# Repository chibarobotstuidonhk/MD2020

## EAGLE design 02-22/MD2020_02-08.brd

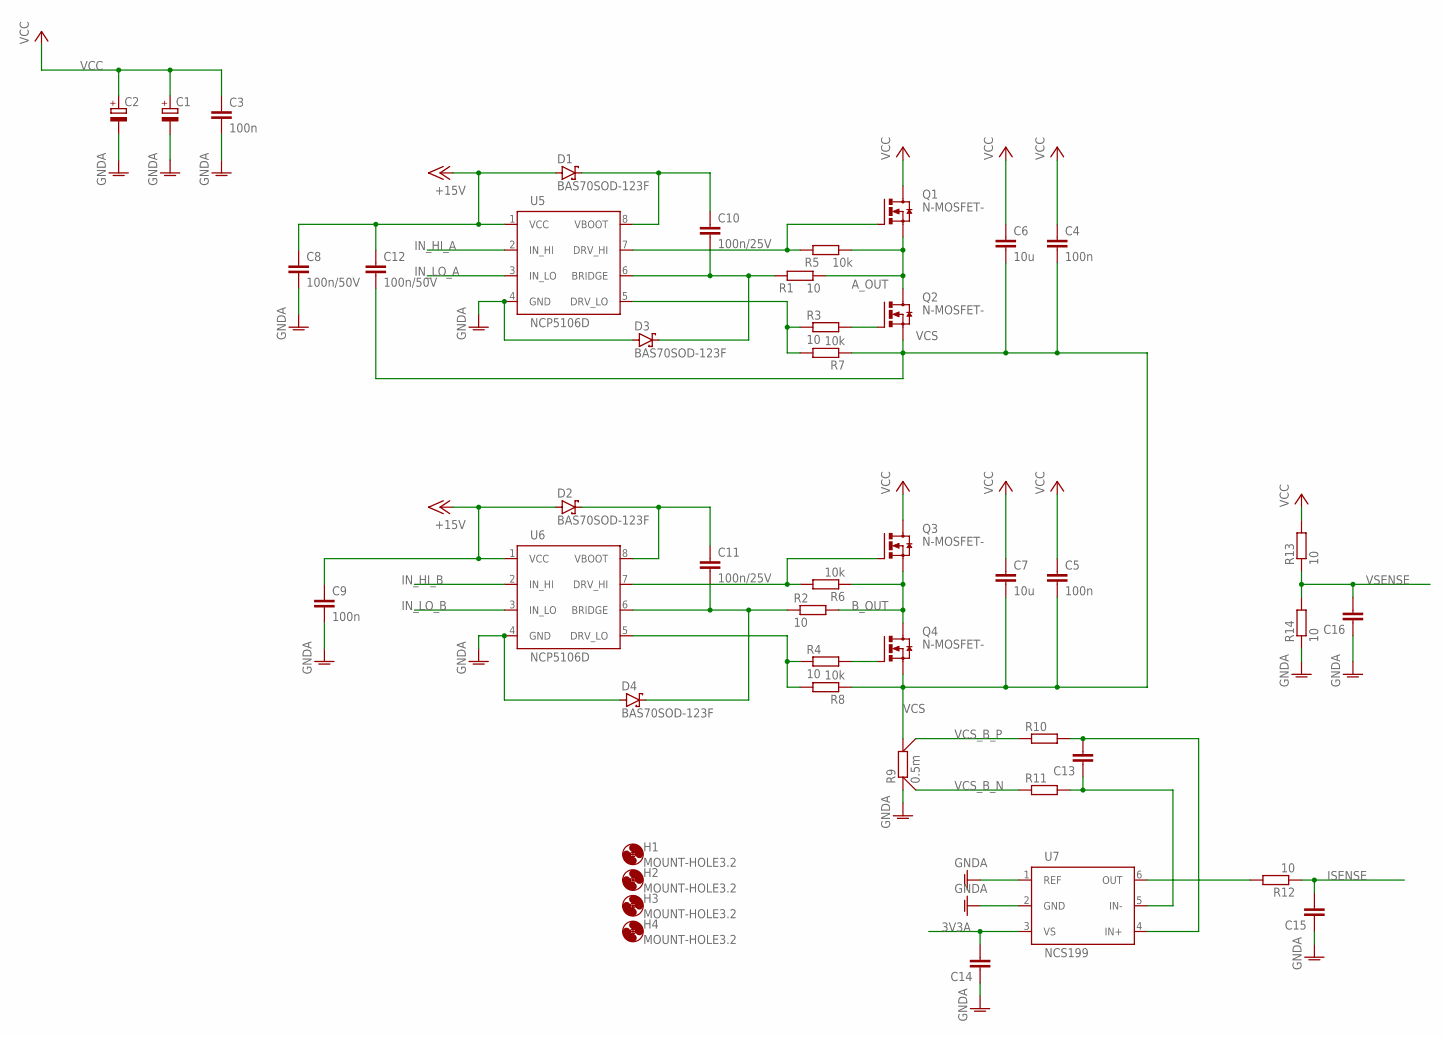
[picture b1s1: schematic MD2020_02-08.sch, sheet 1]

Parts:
C1, C2: CPOL-EUE5-10.5; E5-10,5
C3, C4, C5, C9: 100n; C0603; MPN CC0603KRX7R9BB104
C6, C7: 10u; C1210; MPN CL31A106KBHNNNE
C8, C12: 100n/50V; C0603; MPN CC0603KRX7R9BB104
C10, C11: 100n/25V; C0603; MPN CC0603KRX7R9BB104
C13, C14, C15, C16: C-EUC0603; C0603
D1, D2, D3, D4: BAS70SOD-123F; SOD123F; MPN PMEG4010EH,115
H1, H2, H3, H4: MOUNT-HOLE3.2; 3,2
Q1, Q2, Q3, Q4: N-MOSFET-; SOT669
R1, R2, R3, R4, R12, R13, R14: 10; R0603; MPN RC0603FR-0710RL
R5, R6, R7, R8: 10k; R0603; MPN RC0603FR-0710KL
R9: 0.5m; CSS2H-2512
R10, R11: R-EU_R0603; R0603
U5, U6: NCP5106D; SOIC127P600X175-8
U7: NCS199; SOT65P210X110-6

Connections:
3V3A: C14.2, U7.3 (VS); also elsewhere on the board
+15V: C8.1, C9.1, C12.1, D1.A, D2.A, U5.1 (VCC), U6.1 (VCC); also elsewhere on the board
A_OUT: Q1.1 (SOURCE), Q1.2 (SOURCE), Q1.3 (SOURCE), Q2.5 (DRAIN), R1.2, R5.1
B_OUT: Q3.1 (SOURCE), Q3.2 (SOURCE), Q3.3 (SOURCE), Q4.5 (DRAIN), R2.2, R6.1
GNDA: C1.-, C2.-, C3.2, C8.2, C9.2, C14.1, C15.1, C16.1, D3.A, D4.A, R9.1$1 (1), R9.1$2 (1), R14.1, U5.4 (GND), U6.4 (GND), U7.1 (REF), U7.2 (GND); also elsewhere on the board
IN_HI_A: U5.2 (IN_HI); also elsewhere on the board
IN_HI_B: U6.2 (IN_HI); also elsewhere on the board
IN_LO_A: U5.3 (IN_LO); also elsewhere on the board
IN_LO_B: U6.3 (IN_LO); also elsewhere on the board
ISENSE: C15.2, R12.1; also elsewhere on the board
unnamed: Q1.4 (GATE), R5.2, U5.7 (DRV_HI)
unnamed: Q3.4 (GATE), R6.2, U6.7 (DRV_HI)
unnamed: C10.2, D3.C, R1.1, U5.6 (BRIDGE)
unnamed: R4.1, R8.2, U6.5 (DRV_LO)
unnamed: R12.2, U7.6 (OUT)
unnamed: R3.1, R7.2, U5.5 (DRV_LO)
unnamed: C11.2, D4.C, R2.1, U6.6 (BRIDGE)
unnamed: C13.2, R10.2, U7.4 (IN+)
unnamed: C13.1, R11.2, U7.5 (IN-)
unnamed: Q2.4 (GATE), R3.2
unnamed: Q4.4 (GATE), R4.2
unnamed: C11.1, D2.C, U6.8 (VBOOT)
unnamed: C10.1, D1.C, U5.8 (VBOOT)
VCC: C1.+, C2.+, C3.1, C4.1, C5.1, C6.1, C7.1, Q1.5 (DRAIN), Q3.5 (DRAIN), R13.2; also elsewhere on the board
VCS: C4.2, C5.2, C6.2, C7.2, C12.2, Q2.1 (SOURCE), Q2.2 (SOURCE), Q2.3 (SOURCE), Q4.1 (SOURCE), Q4.2 (SOURCE), Q4.3 (SOURCE), R7.1, R8.1, R9.2$1 (2), R9.2$2 (2)
VCS_B_N: R9.1S, R11.1
VCS_B_P: R9.2S, R10.1
VSENSE: C16.2, R13.1, R14.2; also elsewhere on the board

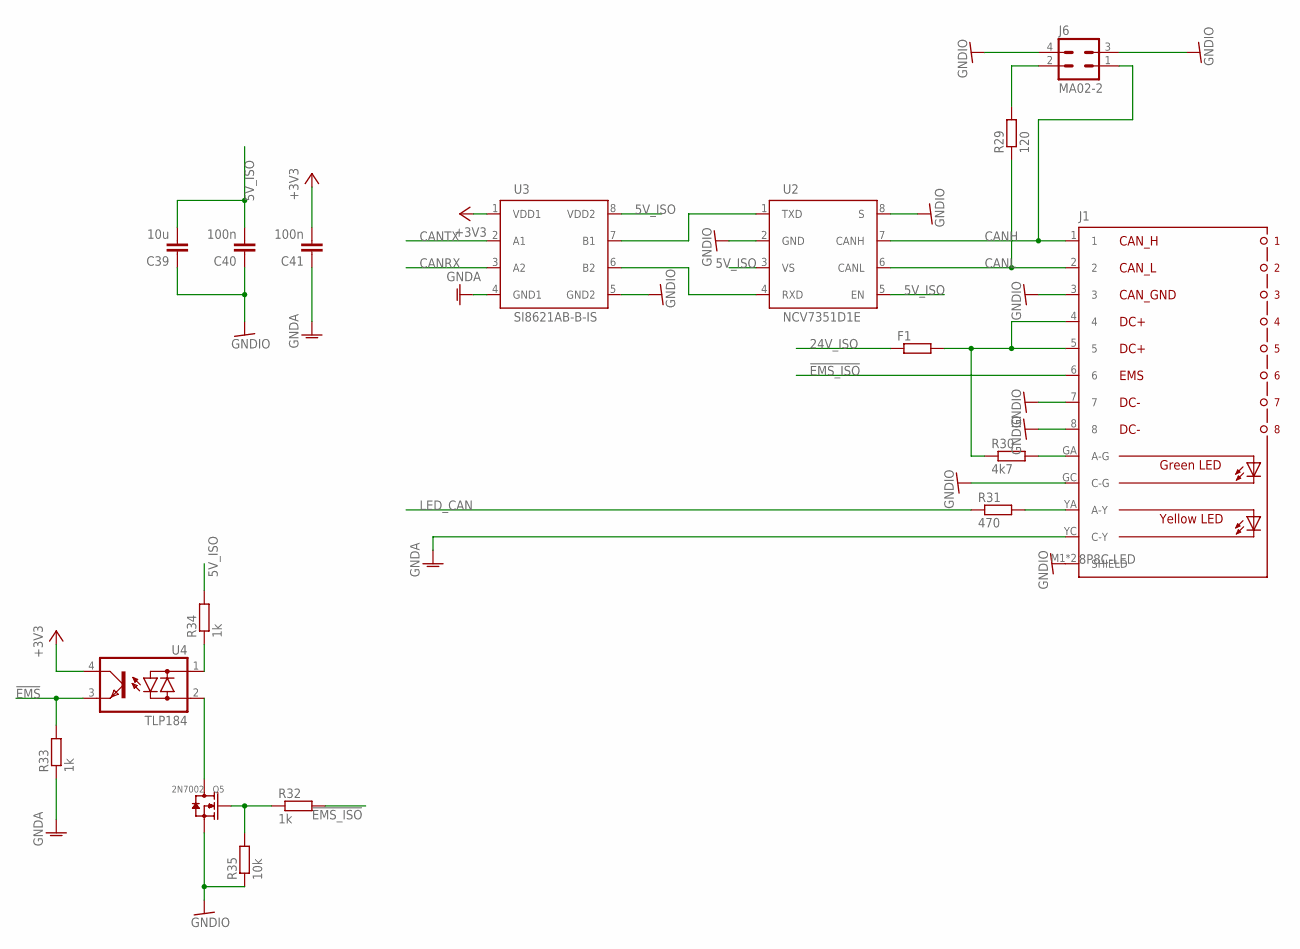
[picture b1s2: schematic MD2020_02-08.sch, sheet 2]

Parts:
C39: 10u; C0805; MPN CC0805ZKY5V6BB106
C40, C41: 100n; C0603; MPN CC0603KRX7R9BB104
F1: R-EU_R1206; R1206
J1: 8P8C-LED
J6: MA02-2; MA02-2W
Q5: 2N7002; SOT-23
R29: 120; R0603; MPN RC0603JR-07120RL
R30: 4k7; R0603; MPN RC0603FR-074K7L
R31: 470; R0603; MPN RC0603JR-07470RL
R32, R33, R34: 1k; R0603; MPN RC0603FR-071KL
R35: 10k; R0603; MPN RC0603FR-0710KL
U2: NCV7351D1E; SO08
U3: SI8621AB-B-IS; SO08
U4: TLP184; 11-4M1S

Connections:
5V_ISO: C39.2, C40.2, R34.2, U2.3 (VS), U2.5 (EN), U3.8 (VDD2); also elsewhere on the board
24V_ISO: F1.1; also elsewhere on the board
!EMS: R33.2, U4.3 (E); also elsewhere on the board
!EMS_ISO: J1.6, R32.2
+3V3: C41.2, U3.1 (VDD1), U4.4 (C); also elsewhere on the board
CANH: J1.1, J6.1, U2.7 (CANH)
CANL: J1.2, R29.1, U2.6 (CANL)
CANRX: U3.3 (A2); also elsewhere on the board
CANTX: U3.2 (A1); also elsewhere on the board
GNDA: C41.1, J1.YC (C-Y), R33.1, U3.4 (GND1); also elsewhere on the board
GNDIO: C39.1, C40.1, J1.3, J1.7, J1.8, J1.GC (C-G), J1.M1 (SHIELD), J1.M2 (SHIELD), J6.3, J6.4, Q5.2 (S), R35.1, U2.2 (GND), U2.8 (S), U3.5 (GND2); also elsewhere on the board
LED_CAN: R31.1; also elsewhere on the board
unnamed: F1.2, J1.4, J1.5, R30.1
unnamed: J6.2, R29.2
unnamed: J1.GA (A-G), R30.2
unnamed: J1.YA (A-Y), R31.2
unnamed: Q5.1 (G), R32.1, R35.2
unnamed: U2.1 (TXD), U3.7 (B1)
unnamed: U2.4 (RXD), U3.6 (B2)
unnamed: Q5.3 (D), U4.2 (AC2)
unnamed: R34.1, U4.1 (AC1)

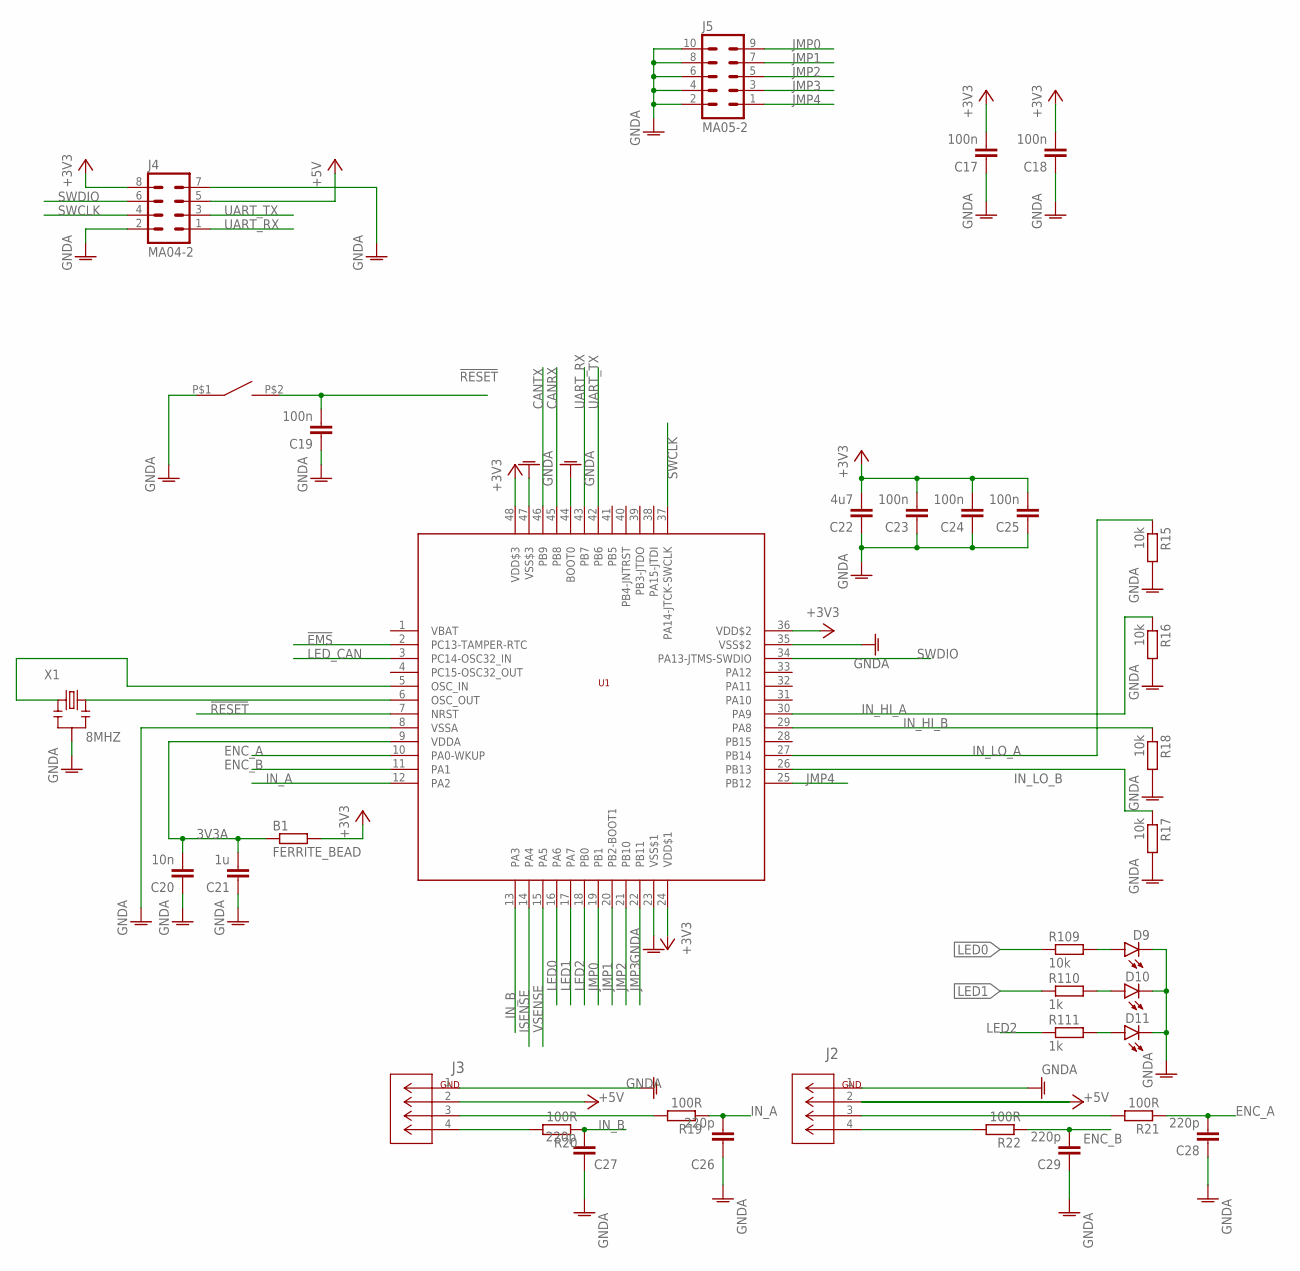
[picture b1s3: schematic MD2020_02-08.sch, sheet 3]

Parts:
B1: FERRITE_BEAD; R0603
C17, C18, C19, C23, C24, C25: 100n; C0603; MPN CC0603KRX7R9BB104
C20: 10n; C0603
C21: 1u; C0603; MPN CC0603KRX7R8BB105
C22: 4u7; C0805; MPN CC0603KRX5R6BB475
C26, C27, C28, C29: 220p; C0603; MPN CL10B221KB8NNNC
D9, D10, D11: LEDCHIPLED_0805; CHIPLED_0805
J2, J3: 1744426-4; CONN4_1744426-4
J4: MA04-2; MA04-2W
J5: MA05-2; MA05-2W
R15, R16, R17, R18, R109: 10k; R0603; MPN RC0603FR-0710KL
R19, R20, R21, R22: 100R; R0603; MPN RC0603JR-07100RL
R110, R111: 1k; R0603; MPN RC0603FR-071KL
S1: SWITCH_TACTILETOP; SWITCH_TACTILE_3X6
U1: STM32F103C8; LQFP48; MPN STM32F103C8T6
X1: 8MHZ; X3-SMD-3.6X1.3X0.8MM; MPN CSTCE8M00G55-RO

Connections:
3V3A: B1.1, C20.2, C21.2, U1.9 (VDDA); also elsewhere on the board
!EMS: U1.2 (PC13-TAMPER-RTC); also elsewhere on the board
!RESET: C19.2, S1.P$2 (2), U1.7 (NRST)
+3V3: B1.2, C17.2, C18.2, C22.2, C23.2, C24.2, C25.2, J4.8, U1.24 (VDD$1), U1.36 (VDD$2), U1.48 (VDD$3); also elsewhere on the board
+5V: J2.2, J3.2, J4.5; also elsewhere on the board
CANRX: U1.45 (PB8); also elsewhere on the board
CANTX: U1.46 (PB9); also elsewhere on the board
ENC_A: C28.2, R21.1, U1.10 (PA0-WKUP)
ENC_B: C29.2, R22.1, U1.11 (PA1)
GNDA: C17.1, C18.1, C19.1, C20.1, C21.1, C22.1, C23.1, C24.1, C25.1, C26.1, C27.1, C28.1, C29.1, D9.C, D10.C, D11.C, J2.1, J3.1, J4.2, J4.7, J5.2, J5.4, J5.6, J5.8, J5.10, R15.2, R16.2, R17.2, R18.2, S1.P$1 (1), U1.8 (VSSA), U1.23 (VSS$1), U1.35 (VSS$2), U1.44 (BOOT0), U1.47 (VSS$3), X1.2; also elsewhere on the board
IN_A: C26.2, R19.1, U1.12 (PA2)
IN_B: C27.2, R20.1, U1.13 (PA3)
IN_HI_A: R16.1, U1.30 (PA9); also elsewhere on the board
IN_HI_B: R18.1, U1.29 (PA8); also elsewhere on the board
IN_LO_A: R15.1, U1.27 (PB14); also elsewhere on the board
IN_LO_B: R17.1, U1.26 (PB13); also elsewhere on the board
ISENSE: U1.14 (PA4); also elsewhere on the board
JMP0: J5.9, U1.19 (PB1)
JMP1: J5.7, U1.20 (PB2-BOOT1)
JMP2: J5.5, U1.21 (PB10)
JMP3: J5.3, U1.22 (PB11)
JMP4: J5.1, U1.25 (PB12)
LED0: R109.1, U1.16 (PA6)
LED1: R110.1, U1.17 (PA7)
LED2: R111.1, U1.18 (PB0)
LED_CAN: U1.3 (PC14-OSC32_IN); also elsewhere on the board
unnamed: D10.A, R110.2
unnamed: D9.A, R109.2
unnamed: U1.6 (OSC_OUT), X1.3
unnamed: J2.4, R22.2
unnamed: J3.4, R20.2
unnamed: J2.3, R21.2
unnamed: J3.3, R19.2
unnamed: U1.5 (OSC_IN), X1.1
unnamed: D11.A, R111.2
SWCLK: J4.4, U1.37 (PA14-JTCK-SWCLK)
SWDIO: J4.6, U1.34 (PA13-JTMS-SWDIO)
UART_RX: J4.1, U1.43 (PB7)
UART_TX: J4.3, U1.42 (PB6)
VSENSE: U1.15 (PA5); also elsewhere on the board

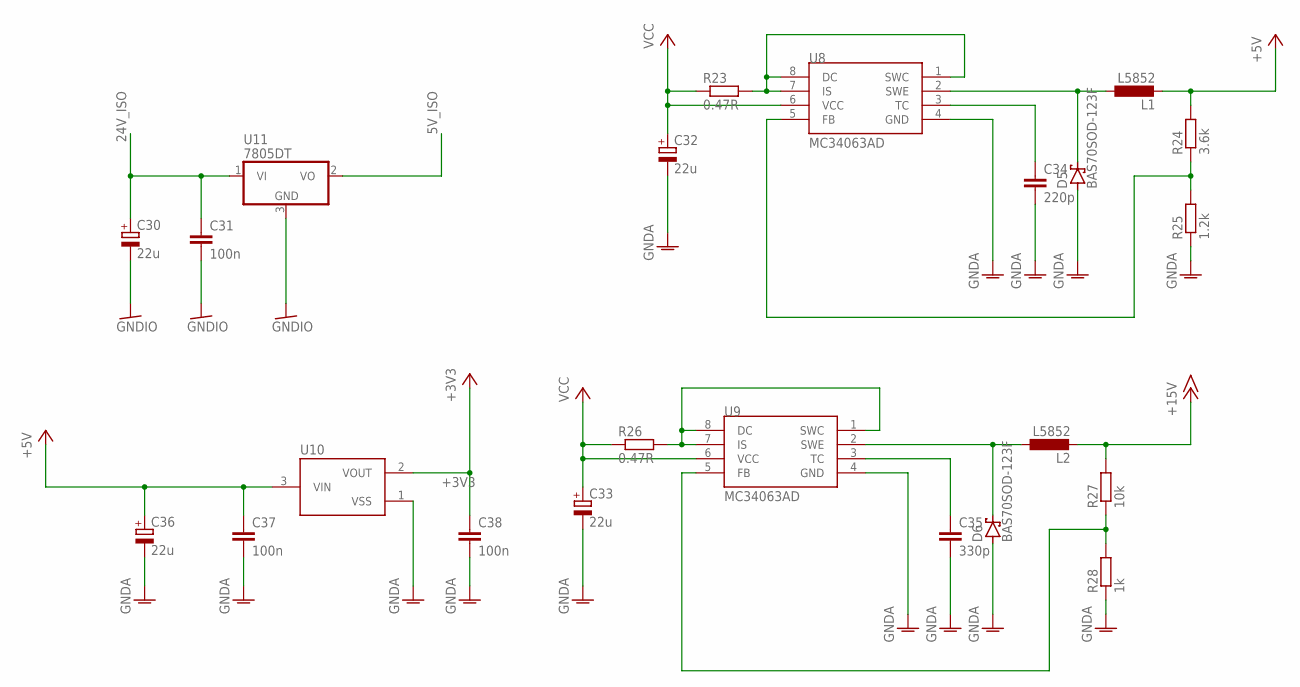
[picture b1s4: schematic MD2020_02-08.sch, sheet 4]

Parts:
C30, C36: 22u; E2,5-5
C31, C37, C38: 100n; C0603; MPN CC0603KRX7R9BB104
C32, C33: 22u; E2-5
C34: 220p; C0603; MPN CL10B221KB8NNNC
C35: 330p; C0603; MPN CL10B331KB8NNNC
D5, D6: BAS70SOD-123F; SOD123F; MPN PMEG4010EH,115
L1, L2: L5852
R23, R26: 0.47R; R0603; MPN 0603WAF470LT5E
R24: 3.6k; R0603; MPN RC0603JR-073K6L
R25: 1.2k; R0603; MPN RC0603JR-071K2L
R27: 10k; R0603; MPN RC0603FR-0710KL
R28: 1k; R0603; MPN RC0603FR-071KL
U8, U9: MC34063AD; SOIC8; MPN MC34063ADR2G
U10: XC6206; SOT95P240X110-3
U11: 7805DT; TO252

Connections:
5V_ISO: U11.2 (VO); also elsewhere on the board
24V_ISO: C30.+, C31.1, U11.1 (VI); also elsewhere on the board
+3V3: C38.1, U10.2 (VOUT); also elsewhere on the board
+5V: C36.+, C37.1, L1.P$2 (2), R24.2, U10.3 (VIN); also elsewhere on the board
+15V: L2.P$2 (2), R27.2; also elsewhere on the board
GNDA: C32.-, C33.-, C34.2, C35.2, C36.-, C37.2, C38.2, D5.A, D6.A, R25.1, R28.1, U8.4 (GND), U9.4 (GND), U10.1 (VSS); also elsewhere on the board
GNDIO: C30.-, C31.2, U11.3 (GND); also elsewhere on the board
unnamed: R23.2, U8.1 (SWC), U8.7 (IS), U8.8 (DC)
unnamed: D5.C, L1.P$1 (1), U8.2 (SWE)
unnamed: C34.1, U8.3 (TC)
unnamed: R24.1, R25.2, U8.5 (FB)
unnamed: R26.2, U9.1 (SWC), U9.7 (IS), U9.8 (DC)
unnamed: D6.C, L2.P$1 (1), U9.2 (SWE)
unnamed: C35.1, U9.3 (TC)
unnamed: R27.1, R28.2, U9.5 (FB)
VCC: C32.+, C33.+, R23.1, R26.1, U8.6 (VCC), U9.6 (VCC); also elsewhere on the board

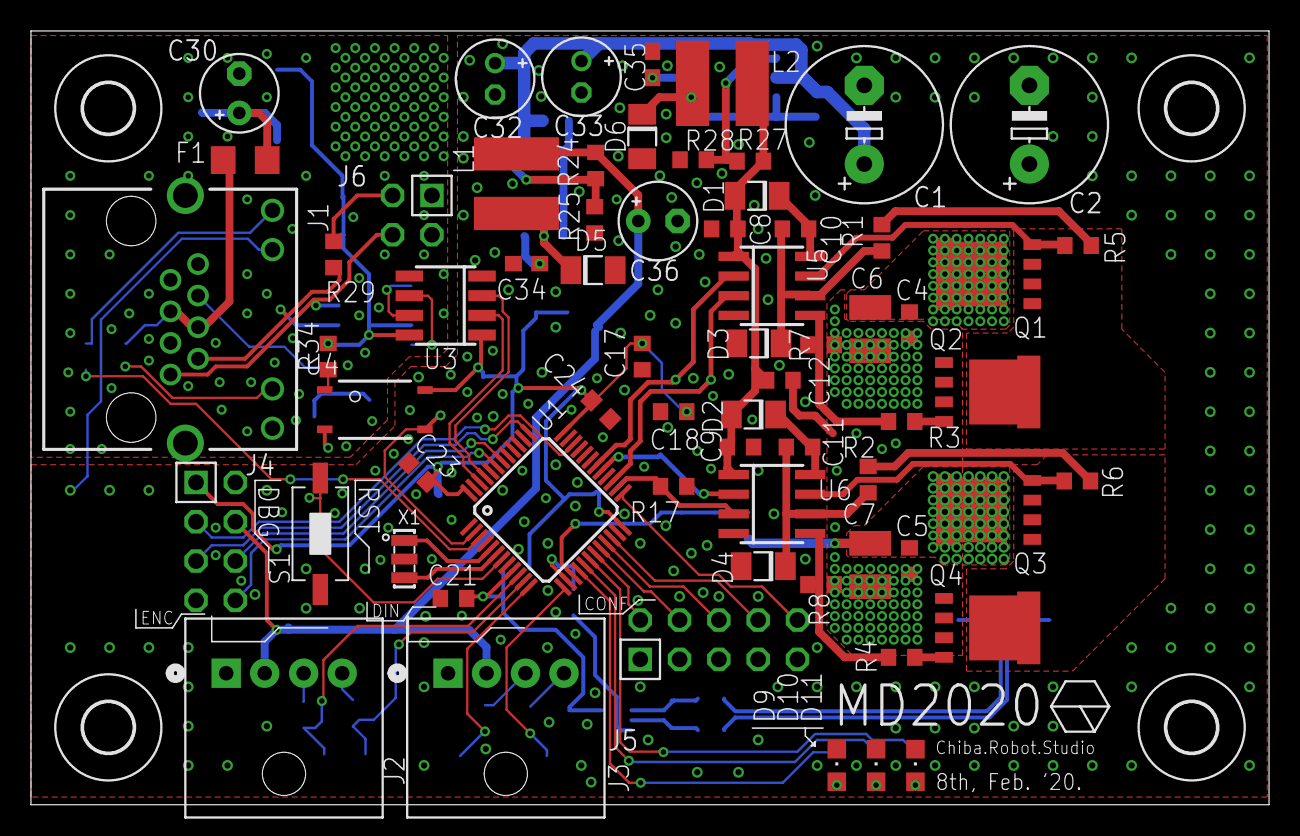
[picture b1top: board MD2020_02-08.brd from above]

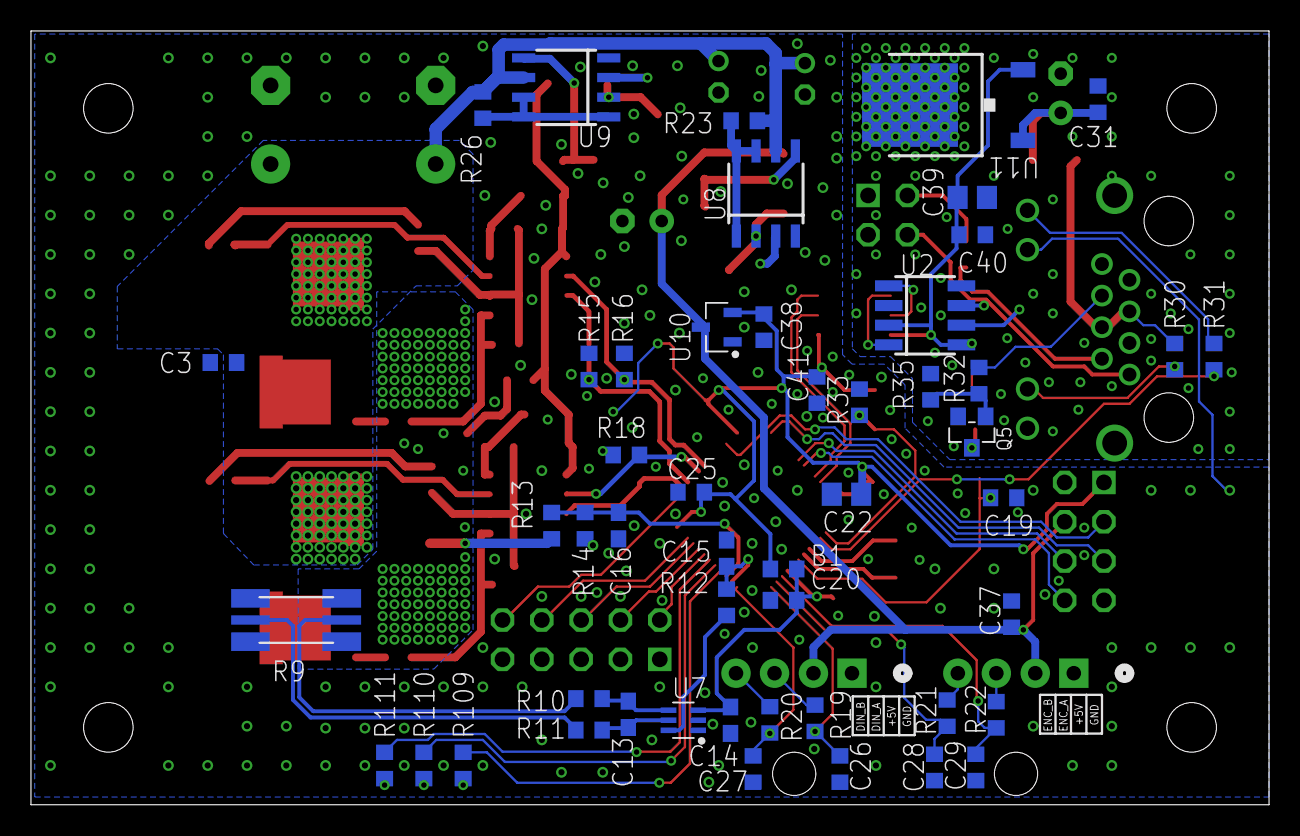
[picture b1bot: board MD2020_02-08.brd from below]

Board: 2 copper layers, 80.0 x 50.0 mm, 120 parts (50 on the bottom side), 83 nets.

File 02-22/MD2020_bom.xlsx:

Part | Value | Device | Package | Description | MPN | 製品詳細セイヒンショウサイ
C3 | 100n | C-EUC0603 | C0603 | CAPACITOR | CC0603KRX7R9BB104 | SMD CAP Ceramic 100nF-50V-10%-X7R
C4 | 100n | C-EUC0603 | C0603 | CAPACITOR | CC0603KRX7R9BB104 | SMD CAP Ceramic 100nF-50V-10%-X7R
C5 | 100n | C-EUC0603 | C0603 | CAPACITOR | CC0603KRX7R9BB104 | SMD CAP Ceramic 100nF-50V-10%-X7R
C6 | 10u | C-EUC1210 | C1210 | CAPACITOR | CL31A106KBHNNNE | 1206 10uF ±10% 50V X5R
C7 | 10u | C-EUC1210 | C1210 | CAPACITOR | CL31A106KBHNNNE | 1206 10uF ±10% 50V X5R
C8 | 100n/50V | C-EUC0603 | C0603 | CAPACITOR | CC0603KRX7R9BB104 | SMD CAP Ceramic 100nF-50V-10%-X7R
C9 | 100n | C-EUC0603 | C0603 | CAPACITOR | CC0603KRX7R9BB104 | SMD CAP Ceramic 100nF-50V-10%-X7R
C10 | 100n/25V | C-EUC0603 | C0603 | CAPACITOR | CC0603KRX7R9BB104 | SMD CAP Ceramic 100nF-50V-10%-X7R
C11 | 100n/25V | C-EUC0603 | C0603 | CAPACITOR | CC0603KRX7R9BB104 | SMD CAP Ceramic 100nF-50V-10%-X7R
C12 | 100n/50V | C-EUC0603 | C0603 | CAPACITOR | CC0603KRX7R9BB104 | SMD CAP Ceramic 100nF-50V-10%-X7R
C17 | 100n | C-EUC0603 | C0603 | CAPACITOR | CC0603KRX7R9BB104 | SMD CAP Ceramic 100nF-50V-10%-X7R
C18 | 100n | C-EUC0603 | C0603 | CAPACITOR | CC0603KRX7R9BB104 | SMD CAP Ceramic 100nF-50V-10%-X7R
C19 | 100n | C-EUC0603 | C0603 | CAPACITOR | CC0603KRX7R9BB104 | SMD CAP Ceramic 100nF-50V-10%-X7R
C21 | 1u | C-EUC0603 | C0603 | CAPACITOR | CC0603KRX7R8BB105 | SMD CAP Ceramic 1uF-25V-10%-X7R
C22 | 4u7 | C-EUC0805 | C0805 | CAPACITOR | CC0603KRX5R6BB475 | SMD CAP Ceramic 4.7uF-10V-10%-X5R;
C23 | 100n | C-EUC0603 | C0603 | CAPACITOR | CC0603KRX7R9BB104 | SMD CAP Ceramic 100nF-50V-10%-X7R
C24 | 100n | C-EUC0603 | C0603 | CAPACITOR | CC0603KRX7R9BB104 | SMD CAP Ceramic 100nF-50V-10%-X7R
C25 | 100n | C-EUC0603 | C0603 | CAPACITOR | CC0603KRX7R9BB104 | SMD CAP Ceramic 100nF-50V-10%-X7R
C26 | 220p | C-EUC0603 | C0603 | CAPACITOR | CL10B221KB8NNNC | 0603 220pF ±10% 50V X7R
C27 | 220p | C-EUC0603 | C0603 | CAPACITOR | CL10B221KB8NNNC | 0603 220pF ±10% 50V X7R
C28 | 220p | C-EUC0603 | C0603 | CAPACITOR | CL10B221KB8NNNC | 0603 220pF ±10% 50V X7R
C29 | 220p | C-EUC0603 | C0603 | CAPACITOR | CL10B221KB8NNNC | 0603 220pF ±10% 50V X7R
C31 | 100n | C-EUC0603 | C0603 | CAPACITOR | CC0603KRX7R9BB104 | SMD CAP Ceramic 100nF-50V-10%-X7R
C34 | 220p | C-EUC0603 | C0603 | CAPACITOR | CL10B221KB8NNNC | 0603 220pF ±10% 50V X7R
C35 | 330p | C-EUC0603 | C0603 | CAPACITOR | CL10B331KB8NNNC | 0603 330pF ±10% 50V X7R
C37 | 100n | C-EUC0603 | C0603 | CAPACITOR | CC0603KRX7R9BB104 | SMD CAP Ceramic 100nF-50V-10%-X7R
C38 | 100n | C-EUC0603 | C0603 | CAPACITOR | CC0603KRX7R9BB104 | SMD CAP Ceramic 100nF-50V-10%-X7R
C39 | 10u | C-EUC0805 | C0805 | CAPACITOR | CC0805ZKY5V6BB106 | SMD CAP Ceramic 10uF-10V-(-20%
C40 | 100n | C-EUC0603 | C0603 | CAPACITOR | CC0603KRX7R9BB104 | SMD CAP Ceramic 100nF-50V-10%-X7R
C41 | 100n | C-EUC0603 | C0603 | CAPACITOR | CC0603KRX7R9BB104 | SMD CAP Ceramic 100nF-50V-10%-X7R
D1 | BAS70SOD-123F | BAS70SOD-123F | SOD123F | Silicon Schottky Diodes | PMEG4010EH,115 | DIODE SCHOTTKY 40V 1A SOD123F
D2 | BAS70SOD-123F | BAS70SOD-123F | SOD123F | Silicon Schottky Diodes | PMEG4010EH,115 | DIODE SCHOTTKY 40V 1A SOD123F
D3 | BAS70SOD-123F | BAS70SOD-123F | SOD123F | Silicon Schottky Diodes | PMEG4010EH,115 | DIODE SCHOTTKY 40V 1A SOD123F
D4 | BAS70SOD-123F | BAS70SOD-123F | SOD123F | Silicon Schottky Diodes | PMEG4010EH,115 | DIODE SCHOTTKY 40V 1A SOD123F
D5 | BAS70SOD-123F | BAS70SOD-123F | SOD123F | Silicon Schottky Diodes | PMEG4010EH,115 | DIODE SCHOTTKY 40V 1A SOD123F
D6 | BAS70SOD-123F | BAS70SOD-123F | SOD123F | Silicon Schottky Diodes | PMEG4010EH,115 | DIODE SCHOTTKY 40V 1A SOD123F
Q5 | 2N7002 | SMD-MOSFET-N-CH-60V-300MA-LOGIC-LEVEL-FET-2N7002(SOT-23) | SOT-23 | 305030028 | 2N7002,215 | SMD MOSFET N-CH 60V 300mA
R1 | 10R | R-EU_R0603 | R0603 | RESISTOR | RC0603FR-0710RL | SMD RES 10R-1%-1/10W
R2 | 10R | R-EU_R0603 | R0603 | RESISTOR | RC0603FR-0710RL | SMD RES 10R-1%-1/10W
R3 | 10R | R-EU_R0603 | R0603 | RESISTOR | RC0603FR-0710RL | SMD RES 10R-1%-1/10W
R4 | 10R | R-EU_R0603 | R0603 | RESISTOR | RC0603FR-0710RL | SMD RES 10R-1%-1/10W
R5 | 10k | R-EU_R0603 | R0603 | RESISTOR | RC0603FR-0710KL | SMD RES 10K-1%-1/10W
R6 | 10k | R-EU_R0603 | R0603 | RESISTOR | RC0603FR-0710KL | SMD RES 10K-1%-1/10W
R7 | 10k | R-EU_R0603 | R0603 | RESISTOR | RC0603FR-0710KL | SMD RES 10K-1%-1/10W
R8 | 10k | R-EU_R0603 | R0603 | RESISTOR | RC0603FR-0710KL | SMD RES 10K-1%-1/10W
R12 | 10R | R-EU_R0603 | R0603 | RESISTOR | RC0603FR-0710RL | SMD RES 10R-1%-1/10W
R13 | 10R | R-EU_R0603 | R0603 | RESISTOR | RC0603FR-0710RL | SMD RES 10R-1%-1/10W
R14 | 10R | R-EU_R0603 | R0603 | RESISTOR | RC0603FR-0710RL | SMD RES 10R-1%-1/10W
R15 | 10k | R-EU_R0603 | R0603 | RESISTOR | RC0603FR-0710KL | SMD RES 10K-1%-1/10W
R16 | 10k | R-EU_R0603 | R0603 | RESISTOR | RC0603FR-0710KL | SMD RES 10K-1%-1/10W
R17 | 10k | R-EU_R0603 | R0603 | RESISTOR | RC0603FR-0710KL | SMD RES 10K-1%-1/10W
R18 | 10k | R-EU_R0603 | R0603 | RESISTOR | RC0603FR-0710KL | SMD RES 10K-1%-1/10W
R19 | 100R | R-EU_R0603 | R0603 | RESISTOR | RC0603JR-07100RL | SMD RES 100R-5%-1/10W
R20 | 100R | R-EU_R0603 | R0603 | RESISTOR | RC0603JR-07100RL | SMD RES 100R-5%-1/10W
R21 | 100R | R-EU_R0603 | R0603 | RESISTOR | RC0603JR-07100RL | SMD RES 100R-5%-1/10W
R22 | 100R | R-EU_R0603 | R0603 | RESISTOR | RC0603JR-07100RL | SMD RES 100R-5%-1/10W
R23 | 0.47R | R-EU_R0603 | R0603 | RESISTOR | 0603WAF470LT5E | 0603 0.47Ω ±1% 1/10W ±800ppm/℃
R24 | 3.6k | R-EU_R0603 | R0603 | RESISTOR | RC0603JR-073K6L | 0603 3.6KΩ ±5% 1/10W ±100ppm/°C
R25 | 1.2k | R-EU_R0603 | R0603 | RESISTOR | RC0603JR-071K2L | 0603 1.2KΩ ±5% 1/10W ±100ppm/°C
R26 | 0.47R | R-EU_R0603 | R0603 | RESISTOR | 0603WAF470LT5E | 0603 0.47Ω ±1% 1/10W ±800ppm/℃
R27 | 10k | R-EU_R0603 | R0603 | RESISTOR | RC0603FR-0710KL | SMD RES 10K-1%-1/10W
R28 | 1k | R-EU_R0603 | R0603 | RESISTOR | RC0603FR-071KL | SMD RES 1K-1%-1/10W
R29 | 120R | R-EU_R0603 | R0603 | RESISTOR | RC0603JR-07120RL | SMD RES 120R-5%-1/10W;0603
R30 | 4k7 | R-EU_R0603 | R0603 | RESISTOR | RC0603FR-074K7L | SMD RES 4.7K-1%-1/10W;0603
R31 | 470R | R-EU_R0603 | R0603 | RESISTOR | RC0603JR-07470RL | SMD RES 470R-5%-1/10W;0603
R32 | 1k | R-EU_R0603 | R0603 | RESISTOR | RC0603FR-071KL | SMD RES 1K-1%-1/10W
R33 | 1k | R-EU_R0603 | R0603 | RESISTOR | RC0603FR-071KL | SMD RES 1K-1%-1/10W
R34 | 1k | R-EU_R0603 | R0603 | RESISTOR | RC0603FR-071KL | SMD RES 1K-1%-1/10W
R35 | 10k | R-EU_R0603 | R0603 | RESISTOR | RC0603FR-0710KL | SMD RES 10K-1%-1/10W
R109 | 10k | R-EU_R0603 | R0603 | RESISTOR | RC0603FR-0710KL | SMD RES 10K-1%-1/10W
R110 | 1k | R-EU_R0603 | R0603 | RESISTOR | RC0603FR-071KL | SMD RES 1K-1%-1/10W
R111 | 1k | R-EU_R0603 | R0603 | RESISTOR | RC0603FR-071KL | SMD RES 1K-1%-1/10W
U1 | STM32F103C8 | STM32F103C8 | LQFP48 | STMicroelectronics STM32F103C8 | STM32F103C8T6 | IC MCU 32BIT 64KB FLASH 48LQFP
U8 | MC34063AD | MC34063AD | SOIC8 |  | MC34063ADR2G | IC REG BUCK BOOST INV ADJ 8SOIC
U9 | MC34063AD | MC34063AD | SOIC8 |  | MC34063ADR2G | IC REG BUCK BOOST INV ADJ 8SOIC
X1 | 8MHZ | SMD-CRYSTAL-8MHZ--0.3%-150R(3P-3.6X1.3MM) | X3-SMD-3.6X1.3X0.8MM | 306010053 | CSTCE8M00G55-RO | SMD Crystal 8MHz-0.3%-150R
